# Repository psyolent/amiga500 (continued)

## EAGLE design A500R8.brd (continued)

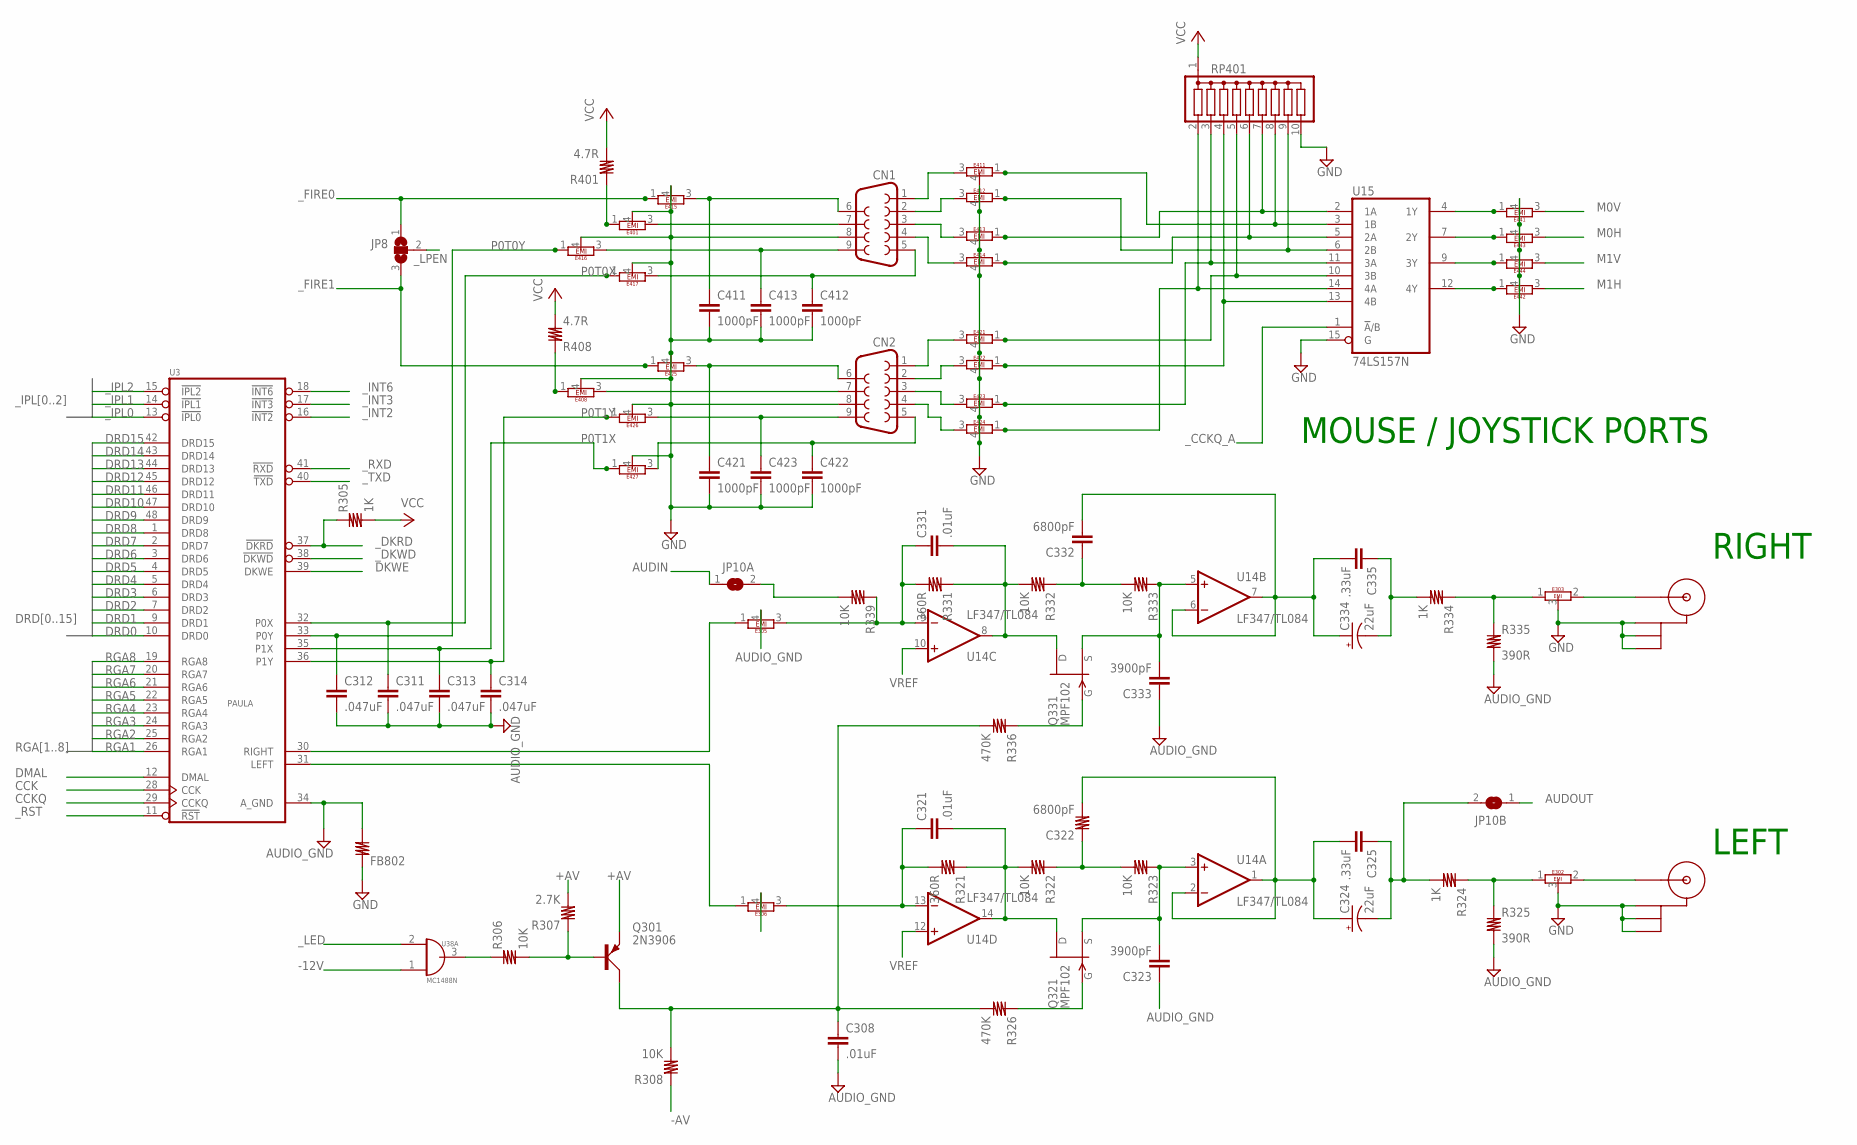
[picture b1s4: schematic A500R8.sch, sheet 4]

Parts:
C308, C321, C331: .01uF; C10B4
C311, C312, C313, C314: .047uF; C10B4
C322: 6800pF; R10B4
C323, C333: 3900pF; C10B4
C324: 22uF; E2,5-6
C325, C335: .33uF; C10B4
C332: 6800pF; C10B4
C334: 22uF; E5-6
C411, C412, C413, C421, C422, C423: 1000pF; C10B4
CN1, CN2: F09HP
CN3: CN4; CINCH-B
CN4: CN3; CINCH-B
E302, E303: EMIFILTER
E305, E306, E401, E408, E411, E412, E413, E414, E415, E416, E417, E421, E422, E423, E424, E425, E426, E427, E441, E442, E443, E444: EMIFILTERLONG; EMIFILTLONG
FB802: R10/4; R10B4
JP8: SJ2W; SJ_2
JP10A, JP10B: SJ
Q301: 2N3906; TO92D
Q321, Q331: MPF102; TO92-
R305, R324, R334: 1K; R10B4
R306, R308, R322, R323, R332, R333, R339: 10K; R10B4
R307: 2.7K; R10B4
R321, R331: 360R; R10B4
R325, R335: 390R; R10B4
R326, R336: 470K; R10B4
R401, R408: 4.7R; R10B4
RP401: G09R; SIL10
U3: PAULA_DIP; DIP48-6
U14: LF347/TL084; DIL14
U15: 74LS157N; DIL16
U38: MC1488N; DIL14

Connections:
+AV: Q301.E, R307.2; also elsewhere on the board
-12V: U38.1 (OE); also elsewhere on the board
-AV: R308.1; also elsewhere on the board
AUDIN: JP10A.1; also elsewhere on the board
AUDIO_GND: C308.2, C311.2, C312.2, C313.2, C314.2, C323.1, C333.1, E305.4, E306.4, FB802.2, R325.2, R335.2, U3.34 (A_GND); also elsewhere on the board
AUDOUT: JP10B.1; also elsewhere on the board
CCK: U3.28 (CCK); also elsewhere on the board
CCKQ: U3.29 (CCKQ); also elsewhere on the board
DKWE: U3.39 (DKWE); also elsewhere on the board
DMAL: U3.12 (DMAL); also elsewhere on the board
DRD0: U3.10 (DRD0); also elsewhere on the board
DRD1: U3.9 (DRD1); also elsewhere on the board
DRD2: U3.7 (DRD2); also elsewhere on the board
DRD3: U3.6 (DRD3); also elsewhere on the board
DRD4: U3.5 (DRD4); also elsewhere on the board
DRD5: U3.4 (DRD5); also elsewhere on the board
DRD6: U3.3 (DRD6); also elsewhere on the board
DRD7: U3.2 (DRD7); also elsewhere on the board
DRD8: U3.1 (DRD8); also elsewhere on the board
DRD9: U3.48 (DRD9); also elsewhere on the board
DRD10: U3.47 (DRD10); also elsewhere on the board
DRD11: U3.46 (DRD11); also elsewhere on the board
DRD12: U3.45 (DRD12); also elsewhere on the board
DRD13: U3.44 (DRD13); also elsewhere on the board
DRD14: U3.43 (DRD14); also elsewhere on the board
DRD15: U3.42 (DRD15); also elsewhere on the board
GND: C411.2, C412.2, C413.2, C421.2, C422.2, C423.2, CN1.8, CN2.8, CN3.P$2, CN3.P$3, CN3.P$4, CN4.P$2, CN4.P$3, CN4.P$4, E302.3, E303.3, E401.4, E408.4, E411.4, E412.4, E413.4, E414.4, E415.4, E416.4, E417.4, E421.4, E422.4, E423.4, E424.4, E425.4, E426.4, E427.4, E441.4, E442.4, E443.4, E444.4, FB802.1, RP401.10, U15.15 (G); also elsewhere on the board
M0H: E443.3; also elsewhere on the board
M0V: E441.3; also elsewhere on the board
M1H: E442.3; also elsewhere on the board
M1V: E444.3; also elsewhere on the board
unnamed: E408.1, E408.2, R408.1
unnamed: E401.1, E401.2, R401.1
unnamed: C411.1, CN1.6, E415.3
unnamed: CN1.7, E401.3
unnamed: C413.1, CN1.9, E416.3
unnamed: C412.1, CN1.5, E417.3
unnamed: CN1.1, E411.3
unnamed: C421.1, CN2.6, E425.3
unnamed: CN2.7, E408.3
unnamed: C423.1, CN2.9, E426.3
unnamed: C422.1, CN2.5, E427.3
unnamed: CN1.2, E412.3
unnamed: CN1.3, E413.3
unnamed: CN1.4, E414.3
unnamed: CN2.1, E421.3
unnamed: CN2.2, E422.3
unnamed: CN2.3, E423.3
unnamed: CN2.4, E424.3
unnamed: E411.1, E411.2, RP401.8, U15.3 (1B)
unnamed: E412.1, E412.2, RP401.9, U15.6 (2B)
unnamed: E413.1, E413.2, RP401.7, U15.2 (1A)
unnamed: E414.1, E414.2, RP401.6, U15.5 (2A)
unnamed: E421.1, E421.2, RP401.5, U15.10 (3B)
unnamed: E422.1, E422.2, RP401.4, U15.13 (4B)
unnamed: E423.1, E423.2, RP401.3, U15.11 (3A)
unnamed: E424.1, E424.2, RP401.2, U15.14 (4A)
unnamed: E441.1, E441.2, U15.4 (1Y)
unnamed: E443.1, E443.2, U15.7 (2Y)
unnamed: E444.1, E444.2, U15.9 (3Y)
unnamed: E442.1, E442.2, U15.12 (4Y)
unnamed: R306.1, U38.3 (O)
unnamed: Q301.B, R306.2, R307.1
unnamed: C308.1, Q301.C, R308.2, R326.2, R336.2
unnamed: E306.1, E306.2, U3.31 (LEFT)
unnamed: E305.1, E305.2, U3.30 (RIGHT)
unnamed: JP10A.2, R339.2
unnamed: C331.1, E305.3, R331.2, R339.1, U14.9 (-IN)
unnamed: C331.2, Q331.3 (D), R331.1, R332.2, U14.8 (OUT)
unnamed: C332.1, R332.1, R333.2
unnamed: Q331.1 (G), R336.1
unnamed: C333.2, Q331.2 (S), R333.1, U14.5 (+IN)
unnamed: C332.2, C334.+, C335.2, U14.6 (-IN), U14.7 (OUT)
unnamed: C321.1, E306.3, R321.2, U14.13 (-IN)
unnamed: C321.2, Q321.3 (D), R321.1, R322.2, U14.14 (OUT)
unnamed: C322.1, R322.1, R323.2
unnamed: C323.2, Q321.2 (S), R323.1, U14.3 (+IN)
unnamed: C322.2, C324.+, C325.2, U14.1 (OUT), U14.2 (-IN)
unnamed: Q321.1 (G), R326.1
unnamed: C324.-, C325.1, JP10B.2, R324.2
unnamed: E302.1, R324.1, R325.1
unnamed: CN3.S, E302.2
unnamed: C334.-, C335.1, R334.2
unnamed: E303.1, R334.1, R335.1
unnamed: CN4.S, E303.2
P0T0X: C311.1, E417.1, E417.2, U3.32 (P0X)
P0T0Y: C312.1, E416.1, E416.2, U3.33 (P0Y)
P0T1X: C313.1, E427.1, E427.2, U3.35 (P1X)
P0T1Y: C314.1, E426.1, E426.2, U3.36 (P1Y)
RGA1: U3.26 (RGA1); also elsewhere on the board
RGA2: U3.25 (RGA2); also elsewhere on the board
RGA3: U3.24 (RGA3); also elsewhere on the board
RGA4: U3.23 (RGA4); also elsewhere on the board
RGA5: U3.22 (RGA5); also elsewhere on the board
RGA6: U3.21 (RGA6); also elsewhere on the board
RGA7: U3.20 (RGA7); also elsewhere on the board
RGA8: U3.19 (RGA8); also elsewhere on the board
VCC: R305.2, R401.2, R408.2, RP401.1; also elsewhere on the board
VREF: U14.10 (+IN), U14.12 (+IN); also elsewhere on the board
_CCKQ_A: U15.1 (!A!/B); also elsewhere on the board
_DKRD: R305.1, U3.37 (!DKRD); also elsewhere on the board
_DKWD: U3.38 (!DKWD); also elsewhere on the board
_FIRE0: E415.1, E415.2, JP8.1; also elsewhere on the board
_FIRE1: E425.1, E425.2, JP8.3; also elsewhere on the board
_INT2: U3.16 (!INT2); also elsewhere on the board
_INT3: U3.17 (!INT3); also elsewhere on the board
_INT6: U3.18 (!INT6); also elsewhere on the board
_IPL0: U3.13 (!IPL0); also elsewhere on the board
_IPL1: U3.14 (!IPL1); also elsewhere on the board
_IPL2: U3.15 (!IPL2); also elsewhere on the board
_LED: U38.2 (I); also elsewhere on the board
_LPEN: JP8.2; also elsewhere on the board
_RST: U3.11 (!RST); also elsewhere on the board
_RXD: U3.41 (!RXD); also elsewhere on the board
_TXD: U3.40 (!TXD); also elsewhere on the board

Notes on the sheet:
MOUSE / JOYSTICK PORTS
RIGHT
LEFT

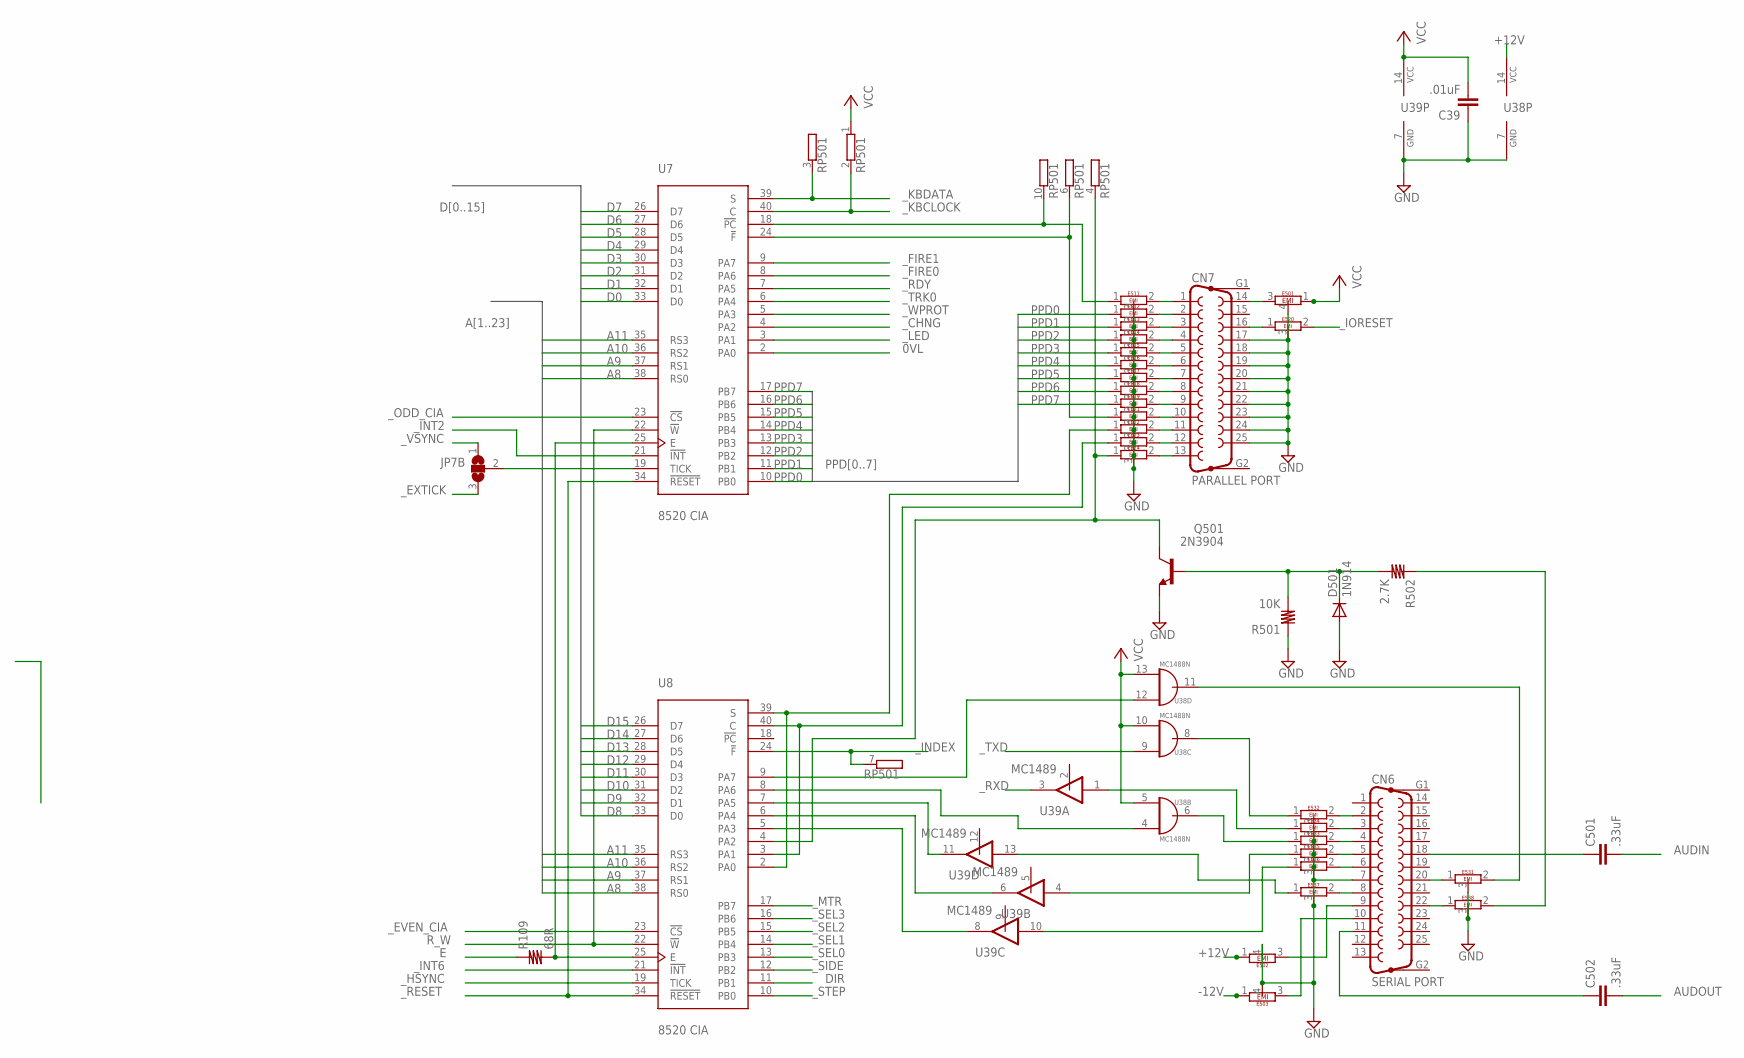
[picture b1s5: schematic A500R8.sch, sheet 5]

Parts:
C39: .01uF; C10B4
C501, C502: .33uF; C10B4
CN6: SERIAL PORT; F25HP
CN7: PARALLEL PORT; F25HP
D501: 1N914; D-10
E501, E502, E503: 47R; EMIFILTLONG
E511, E512, E513, E514, E515, E516, E517, E518, E519, E520, E521, E522, E523, E524, E531, E532, E533, E534, E535, E536, E537, E538: EMIFILTER
JP7B: SJ2W; SJ_2
Q501: 2N3904; TO92
R109: 68R; R10B4
R501: 10K; R10B4
R502: 2.7K; R10B4
RP501: GE09RP; SIL10
U7, U8: 8520 CIA; DIP40-6
U38: MC1488N; DIL14
U39: MC1489; DIL14

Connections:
0VL: U7.2 (PA0); also elsewhere on the board
+12V: E502.1, E502.2, U38.14 (VCC); also elsewhere on the board
-12V: E503.1, E503.2; also elsewhere on the board
A8: U7.38 (RS0), U8.38 (RS0); also elsewhere on the board
A9: U7.37 (RS1), U8.37 (RS1); also elsewhere on the board
A10: U7.36 (RS2), U8.36 (RS2); also elsewhere on the board
A11: U7.35 (RS3), U8.35 (RS3); also elsewhere on the board
AUDIN: C501.2; also elsewhere on the board
AUDOUT: C502.2; also elsewhere on the board
D0: U7.33 (D0); also elsewhere on the board
D1: U7.32 (D1); also elsewhere on the board
D2: U7.31 (D2); also elsewhere on the board
D3: U7.30 (D3); also elsewhere on the board
D4: U7.29 (D4); also elsewhere on the board
D5: U7.28 (D5); also elsewhere on the board
D6: U7.27 (D6); also elsewhere on the board
D7: U7.26 (D7); also elsewhere on the board
D8: U8.33 (D0); also elsewhere on the board
D9: U8.32 (D1); also elsewhere on the board
D10: U8.31 (D2); also elsewhere on the board
D11: U8.30 (D3); also elsewhere on the board
D12: U8.29 (D4); also elsewhere on the board
D13: U8.28 (D5); also elsewhere on the board
D14: U8.27 (D6); also elsewhere on the board
D15: U8.26 (D7); also elsewhere on the board
DIR: U8.11 (PB1); also elsewhere on the board
E: R109.1; also elsewhere on the board
GND: C39.1, CN6.7, CN7.17, CN7.18, CN7.19, CN7.20, CN7.21, CN7.22, CN7.23, CN7.24, CN7.25, D501.A, E501.4, E502.4, E503.4, E511.3, E512.3, E513.3, E514.3, E515.3, E516.3, E517.3, E518.3, E519.3, E520.3, E521.3, E522.3, E523.3, E524.3, E531.3, E532.3, E533.3, E534.3, E535.3, E536.3, E537.3, E538.3, Q501.3 (E), R501.1, U38.7 (GND), U39.7 (GND); also elsewhere on the board
unnamed: U8.6 (PA4), U39.6 (O)
unnamed: JP7B.2, U7.19 (TICK)
unnamed: U8.9 (PA7), U38.12 (I)
unnamed: E511.1, RP501.10 (2), U7.18 (!PC)
unnamed: E521.1, RP501.6 (2), U7.24 (!F)
unnamed: U8.5 (PA3), U39.8 (O)
unnamed: CN7.1, E511.2
unnamed: CN7.2, E512.2
unnamed: CN7.3, E513.2
unnamed: CN7.4, E514.2
unnamed: CN7.5, E515.2
unnamed: CN7.6, E516.2
unnamed: CN7.7, E517.2
unnamed: CN7.8, E518.2
unnamed: CN7.9, E519.2
unnamed: CN7.10, E521.2
unnamed: CN7.11, E522.2
unnamed: CN7.12, E523.2
unnamed: CN7.13, E524.2
unnamed: E522.1, U8.2 (PA0), U8.39 (S)
unnamed: E523.1, U8.3 (PA1), U8.40 (C)
unnamed: E524.1, Q501.1 (C), RP501.4 (2), U8.4 (PA2)
unnamed: U8.7 (PA5), U39.11 (O)
unnamed: U8.8 (PA6), U38.4 (OE)
unnamed: E534.1, U39.1 (OE)
unnamed: E536.1, U39.10 (OE)
unnamed: E535.1, U39.4 (OE)
unnamed: E537.1, U39.13 (OE)
unnamed: U38.5 (I), U38.10 (OE), U38.13 (OE)
unnamed: CN6.8, E537.2
unnamed: E531.2, U38.11 (O)
unnamed: CN6.2, E532.2
unnamed: CN6.3, E534.2
unnamed: CN6.4, E533.2
unnamed: CN6.5, E535.2
unnamed: CN6.6, E536.2
unnamed: E532.1, U38.8 (O)
unnamed: CN6.20, E531.1
unnamed: CN6.22, E538.1
unnamed: E538.2, R502.1
unnamed: C501.1, CN6.18
unnamed: C502.1, CN6.11
unnamed: E533.1, U38.6 (O)
unnamed: CN6.9, E502.3
unnamed: CN7.16, E520.1
unnamed: D501.C, Q501.2 (B), R501.2, R502.2
unnamed: CN6.10, E503.3
unnamed: CN7.14, E501.3
unnamed: R109.2, U7.25 (E), U8.25 (E)
PPD0: E512.1, U7.10 (PB0)
PPD1: E513.1, U7.11 (PB1)
PPD2: E514.1, U7.12 (PB2)
PPD3: E515.1, U7.13 (PB3)
PPD4: E516.1, U7.14 (PB4)
PPD5: E517.1, U7.15 (PB5)
PPD6: E518.1, U7.16 (PB6)
PPD7: E519.1, U7.17 (PB7)
R_W: U7.22 (!W), U8.22 (!W); also elsewhere on the board
VCC: C39.2, E501.1, E501.2, RP501.1, U39.14 (VCC); also elsewhere on the board
_CHNG: U7.4 (PA2); also elsewhere on the board
_EVEN_CIA: U8.23 (!CS); also elsewhere on the board
_EXTICK: JP7B.3; also elsewhere on the board
_FIRE0: U7.8 (PA6); also elsewhere on the board
_FIRE1: U7.9 (PA7); also elsewhere on the board
_HSYNC: U8.19 (TICK); also elsewhere on the board
_INDEX: RP501.7 (2), U8.24 (!F); also elsewhere on the board
_INT2: U7.21 (!INT); also elsewhere on the board
_INT6: U8.21 (!INT); also elsewhere on the board
_IORESET: E520.2; also elsewhere on the board
_KBCLOCK: RP501.2, U7.40 (C); also elsewhere on the board
_KBDATA: RP501.3 (2), U7.39 (S); also elsewhere on the board
_LED: U7.3 (PA1); also elsewhere on the board
_MTR: U8.17 (PB7); also elsewhere on the board
_ODD_CIA: U7.23 (!CS); also elsewhere on the board
_RDY: U7.7 (PA5); also elsewhere on the board
_RESET: U7.34 (!RESET), U8.34 (!RESET); also elsewhere on the board
_RXD: U39.3 (O); also elsewhere on the board
_SEL0: U8.13 (PB3); also elsewhere on the board
_SEL1: U8.14 (PB4); also elsewhere on the board
_SEL2: U8.15 (PB5); also elsewhere on the board
_SEL3: U8.16 (PB6); also elsewhere on the board
_SIDE: U8.12 (PB2); also elsewhere on the board
_STEP: U8.10 (PB0); also elsewhere on the board
_TRK0: U7.6 (PA4); also elsewhere on the board
_TXD: U38.9 (I); also elsewhere on the board
_VSYNC: JP7B.1; also elsewhere on the board
_WPROT: U7.5 (PA3); also elsewhere on the board

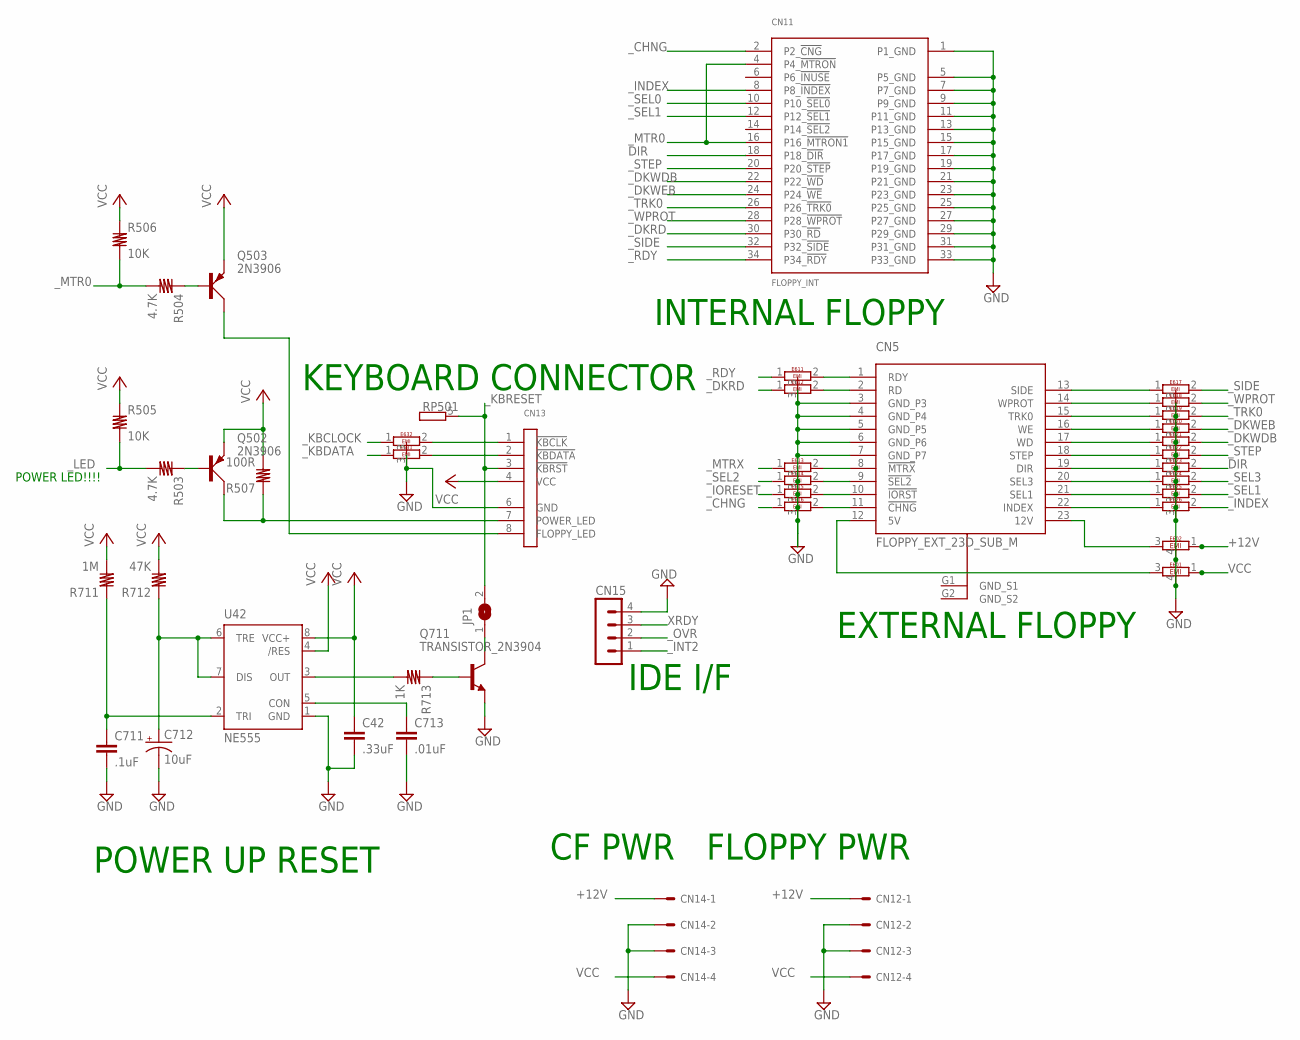
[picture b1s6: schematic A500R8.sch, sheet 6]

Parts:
C42: .33uF; C10B4
C711: .1uF; C10B4
C712: 10uF; E5-6
C713: .01uF; C10B4
CN5: FLOPPY_EXT_23D_SUB_M; M23H_FC
CN11: FLOPPY_INT; 2X17M
CN12, CN14: 22-27-2041-04; 6410-04
CN13: KB_A500; 1X08S
CN15: MA04-1
E601, E602: EMIFILTERLONG; EMIFILTLONG
E611, E612, E613, E614, E615, E616, E617, E618, E619, E620, E621, E622, E623, E624, E625, E626, E631, E632: EMIFILTER
JP1: SJ
Q502, Q503: 2N3906; TO92D
Q711: TRANSISTOR_2N3904; TRANSISTOR_TO92-ECB
R503, R504: 4.7K; R10B4
R505, R506: 10K; R10B4
R507: 100R; R10B4
R711: 1M; R10B4
R712: 47K; R10B4
R713: 1K; R10B4
RP501: GE09RP; SIL10
U42: NE555; DIL-08

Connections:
+12V: CN12.1, CN14.1, E602.1, E602.2; also elsewhere on the board
DIR: CN11.18 (P18_!DIR), E623.2; also elsewhere on the board
GND: C42.2, C711.2, C712.-, C713.2, CN5.3 (GND_P3), CN5.4 (GND_P4), CN5.5 (GND_P5), CN5.6 (GND_P6), CN5.7 (GND_P7), CN11.1 (P1_GND), CN11.5 (P5_GND), CN11.7 (P7_GND), CN11.9 (P9_GND), CN11.11 (P11_GND), CN11.13 (P13_GND), CN11.15 (P15_GND), CN11.17 (P17_GND), CN11.19 (P19_GND), CN11.21 (P21_GND), CN11.23 (P23_GND), CN11.25 (P25_GND), CN11.27 (P27_GND), CN11.29 (P29_GND), CN11.31 (P31_GND), CN11.33 (P33_GND), CN12.2, CN12.3, CN14.2, CN14.3, CN15.4, E601.4, E602.4, E611.3, E612.3, E613.3, E614.3, E615.3, E616.3, E617.3, E618.3, E619.3, E620.3, E621.3, E622.3, E623.3, E624.3, E625.3, E626.3, E631.3, E632.3, Q711.1 (E), U42.1 (GND); also elsewhere on the board
GND_S1: CN5.G1 (GND_S1); also elsewhere on the board
GND_S2: CN5.G2 (GND_S2); also elsewhere on the board
unnamed: C711.1, R711.1, U42.2 (TRI)
unnamed: C712.+, R712.1, U42.6 (TRE), U42.7 (DIS)
unnamed: R713.2, U42.3 (OUT)
unnamed: C713.1, U42.5 (CON)
unnamed: Q711.2 (B), R713.1
unnamed: JP1.1, Q711.3 (C)
unnamed: CN13.1 (!KBCLK), E632.2
unnamed: CN13.2 (!KBDATA), E631.2
unnamed: CN13.7 (POWER_LED), Q502.C, R507.1
unnamed: Q502.B, R503.1
unnamed: CN13.8 (FLOPPY_LED), Q503.C
unnamed: Q503.B, R504.1
unnamed: CN5.8 (!MTRX!), E613.2
unnamed: CN5.23 (12V), E602.3
unnamed: CN5.12 (5V), E601.3
unnamed: CN5.13 (SIDE), E617.1
unnamed: CN5.14 (WPROT), E618.1
unnamed: CN5.15 (TRK0), E619.1
unnamed: CN5.16 (WE), E620.1
unnamed: CN5.17 (WD), E621.1
unnamed: CN5.18 (STEP), E622.1
unnamed: CN5.19 (DIR), E623.1
unnamed: CN5.20 (SEL3), E624.1
unnamed: CN5.21 (SEL1), E625.1
unnamed: CN5.22 (INDEX), E626.1
unnamed: CN5.2 (RD), E612.2
unnamed: CN5.1 (RDY), E611.2
unnamed: CN5.9 (!SEL2!), E614.2
unnamed: CN5.10 (!IORST!), E615.2
unnamed: CN5.11 (!CHNG!), E616.2
VCC: C42.1, CN12.4, CN13.4 (VCC), CN14.4, E601.1, E601.2, Q502.E, Q503.E, R505.1, R506.1, R507.2, R711.2, R712.2, U42.4 (/RES), U42.8 (VCC+); also elsewhere on the board
XRDY: CN15.3; also elsewhere on the board
_CHNG: CN11.2 (P2_!CNG!), E616.1; also elsewhere on the board
_DKRD: CN11.30 (P30_!RD), E612.1; also elsewhere on the board
_DKWDB: CN11.22 (P22_!WD), E621.2; also elsewhere on the board
_DKWEB: CN11.24 (P24_!WE), E620.2; also elsewhere on the board
_INDEX: CN11.8 (P8_!INDEX!), E626.2; also elsewhere on the board
_INT2: CN15.1; also elsewhere on the board
_IORESET: E615.1; also elsewhere on the board
_KBCLOCK: E632.1; also elsewhere on the board
_KBDATA: E631.1; also elsewhere on the board
_KBRESET: CN13.3 (!KBRST), JP1.2, RP501.5 (2); also elsewhere on the board
_LED: R503.2, R505.2; also elsewhere on the board
_MTR0: CN11.4 (P4_!MTRON), CN11.16 (P16_!MTRON1), R504.2, R506.2; also elsewhere on the board
_MTRX: E613.1; also elsewhere on the board
_OVR: CN15.2
_RDY: CN11.34 (P34_!RDY), E611.1; also elsewhere on the board
_SEL0: CN11.10 (P10_!SEL0); also elsewhere on the board
_SEL1: CN11.12 (P12_!SEL1), E625.2; also elsewhere on the board
_SEL2: E614.1; also elsewhere on the board
_SEL3: E624.2; also elsewhere on the board
_SIDE: CN11.32 (P32_!SIDE), E617.2; also elsewhere on the board
_STEP: CN11.20 (P20_!STEP), E622.2; also elsewhere on the board
_TRK0: CN11.26 (P26_!TRK0), E619.2; also elsewhere on the board
_WPROT: CN11.28 (P28_!WPROT), E618.2; also elsewhere on the board

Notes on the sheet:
POWER LED!!!!
IDE I/F
CF PWR
FLOPPY PWR
INTERNAL FLOPPY
EXTERNAL FLOPPY
KEYBOARD CONNECTOR
POWER UP RESET

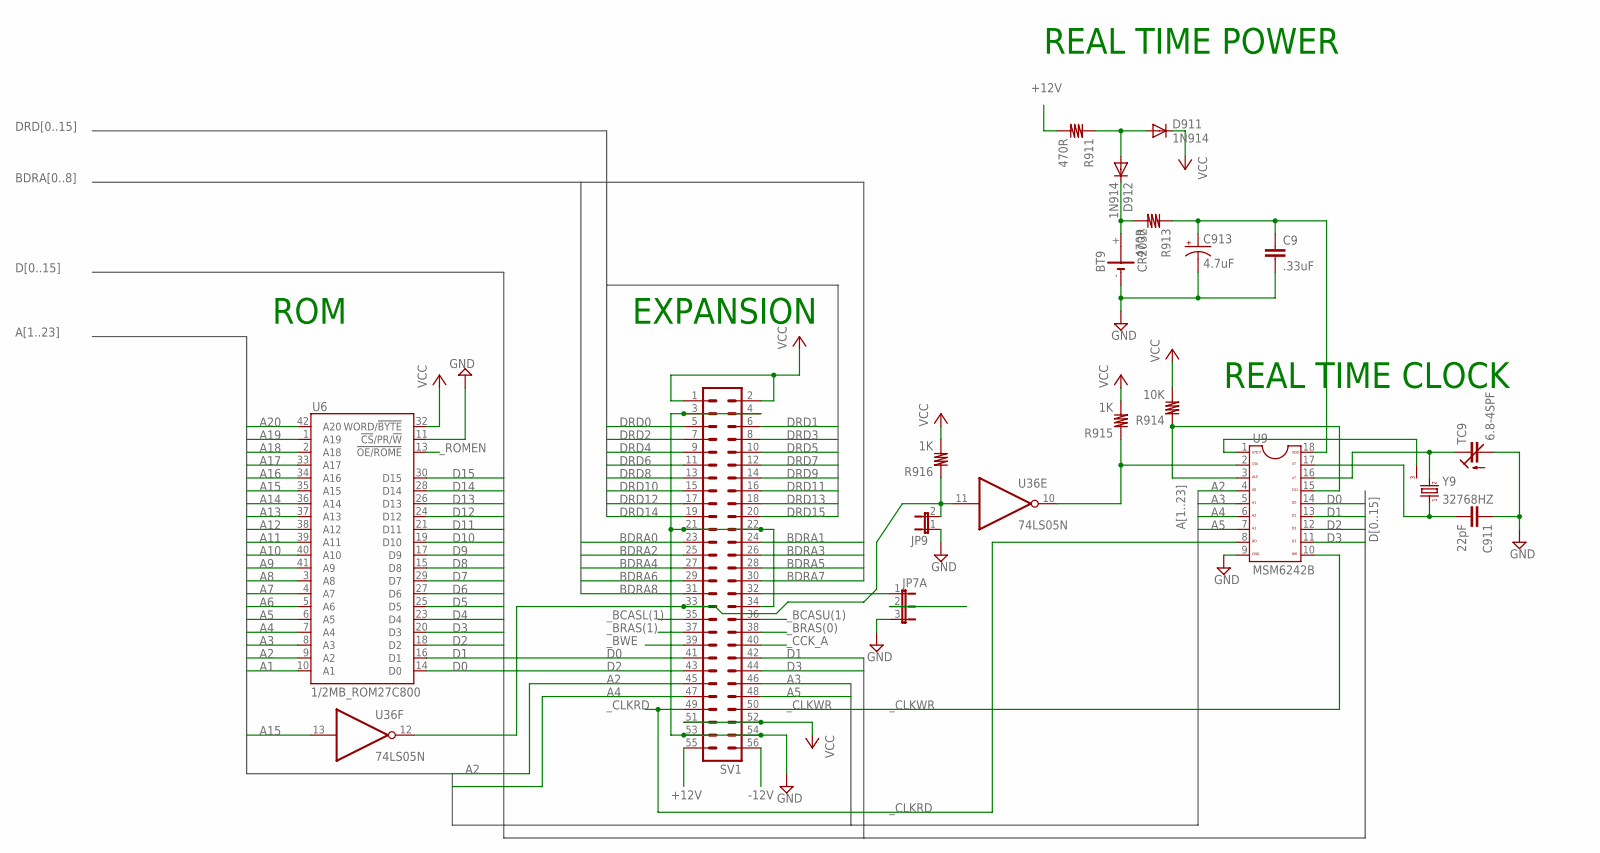
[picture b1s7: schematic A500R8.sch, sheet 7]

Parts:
BT9: CR2032; CR2032H
C9: .33uF; C10B4
C911: 22pF; C10B4
C913: 4.7uF; E5-6
D911, D912: 1N914; DO41-10
JP7A: JP2E; JP2
JP9: JP1E; JP1
R911, R913: 470R; R10B4
R914: 10K; R10B4
R915, R916: 1K; R10B4
SV1: AMIGA56
TC9: 6.8-4SPF; CTRIM3050.504
U6: 1/2MB_ROM27C800; DIP42-6
U9: MSM6242B; DIL18
U36: 74LS05N; DIL14
Y9: 32768HZ; HC49TL-H

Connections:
+12V: R911.2, SV1.55; also elsewhere on the board
-12V: SV1.56; also elsewhere on the board
A1: U6.10 (A1); also elsewhere on the board
A2: SV1.45, U6.9 (A2), U9.4; also elsewhere on the board
A3: SV1.46, U6.8 (A3), U9.5; also elsewhere on the board
A4: SV1.47, U6.7 (A4), U9.6; also elsewhere on the board
A5: SV1.48, U6.6 (A5), U9.7; also elsewhere on the board
A6: U6.5 (A6); also elsewhere on the board
A7: U6.4 (A7); also elsewhere on the board
A8: U6.3 (A8); also elsewhere on the board
A9: U6.41 (A9); also elsewhere on the board
A10: U6.40 (A10); also elsewhere on the board
A11: U6.39 (A11); also elsewhere on the board
A12: U6.38 (A12); also elsewhere on the board
A13: U6.37 (A13); also elsewhere on the board
A14: U6.36 (A14); also elsewhere on the board
A15: U6.35 (A15), U36.13 (I); also elsewhere on the board
A16: U6.34 (A16); also elsewhere on the board
A17: U6.33 (A17); also elsewhere on the board
A18: U6.2 (A18); also elsewhere on the board
A19: U6.1 (A19); also elsewhere on the board
A20: U6.42 (A20); also elsewhere on the board
BDRA0: SV1.23; also elsewhere on the board
BDRA1: SV1.24; also elsewhere on the board
BDRA2: SV1.25; also elsewhere on the board
BDRA3: SV1.26; also elsewhere on the board
BDRA4: SV1.27; also elsewhere on the board
BDRA5: SV1.28; also elsewhere on the board
BDRA6: SV1.29; also elsewhere on the board
BDRA7: SV1.30; also elsewhere on the board
BDRA8: SV1.31; also elsewhere on the board
D0: SV1.41, U6.14 (D0), U9.14; also elsewhere on the board
D1: SV1.42, U6.16 (D1), U9.13; also elsewhere on the board
D2: SV1.43, U6.18 (D2), U9.12; also elsewhere on the board
D3: SV1.44, U6.20 (D3), U9.11; also elsewhere on the board
D4: U6.23 (D4); also elsewhere on the board
D5: U6.25 (D5); also elsewhere on the board
D6: U6.27 (D6); also elsewhere on the board
D7: U6.29 (D7); also elsewhere on the board
D8: U6.15 (D8); also elsewhere on the board
D9: U6.17 (D9); also elsewhere on the board
D10: U6.19 (D10); also elsewhere on the board
D11: U6.21 (D11); also elsewhere on the board
D12: U6.24 (D12); also elsewhere on the board
D13: U6.26 (D13); also elsewhere on the board
D14: U6.28 (D14); also elsewhere on the board
D15: U6.30 (D15); also elsewhere on the board
DRD0: SV1.5; also elsewhere on the board
DRD1: SV1.6; also elsewhere on the board
DRD2: SV1.7; also elsewhere on the board
DRD3: SV1.8; also elsewhere on the board
DRD4: SV1.9; also elsewhere on the board
DRD5: SV1.10; also elsewhere on the board
DRD6: SV1.11; also elsewhere on the board
DRD7: SV1.12; also elsewhere on the board
DRD8: SV1.13; also elsewhere on the board
DRD9: SV1.14; also elsewhere on the board
DRD10: SV1.15; also elsewhere on the board
DRD11: SV1.16; also elsewhere on the board
DRD12: SV1.17; also elsewhere on the board
DRD13: SV1.18; also elsewhere on the board
DRD14: SV1.19; also elsewhere on the board
DRD15: SV1.20; also elsewhere on the board
GND: BT9.-, C9.2, C911.1, C913.-, JP7A.3, JP9.1, SV1.3, SV1.4, SV1.21, SV1.22, SV1.34, SV1.53, SV1.54, TC9.2 (A), U6.11 (!CS!/PR/!W!), U9.9; also elsewhere on the board
unnamed: JP9.2, R916.1, SV1.33, U36.11 (I), U36.12 (O)
unnamed: JP7A.1, SV1.32
unnamed: R915.1, U9.2, U36.10 (O)
unnamed: BT9.+, D912.C, R913.2
unnamed: D911.A, D912.A, R911.1
unnamed: C9.1, C913.+, R913.1, U9.18
unnamed: U9.1, Y9.3
unnamed: TC9.1 (E), U9.16, Y9.2
unnamed: R914.1, U9.3, U9.15
unnamed: C911.2, U9.17, Y9.1
VCC: D911.C, R914.2, R915.2, R916.2, SV1.1, SV1.2, SV1.51, SV1.52, U6.32 (WORD/!BYTE); also elsewhere on the board
_BCASL(1): SV1.35; also elsewhere on the board
_BCASU(1): SV1.36; also elsewhere on the board
_BRAS(0): SV1.38; also elsewhere on the board
_BRAS(1): SV1.37; also elsewhere on the board
_BWE: SV1.39; also elsewhere on the board
_CCK_A: SV1.40; also elsewhere on the board
_CLKRD: SV1.49, U9.8; also elsewhere on the board
_CLKWR: SV1.50, U9.10; also elsewhere on the board
_EXTICK: JP7A.2; also elsewhere on the board
_ROMEN: U6.13 (!OE/ROME); also elsewhere on the board

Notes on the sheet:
REAL TIME POWER
REAL TIME CLOCK
EXPANSION
ROM
